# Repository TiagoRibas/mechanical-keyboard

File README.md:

# mechanical-keyboard
Projetos de teclado mecanico

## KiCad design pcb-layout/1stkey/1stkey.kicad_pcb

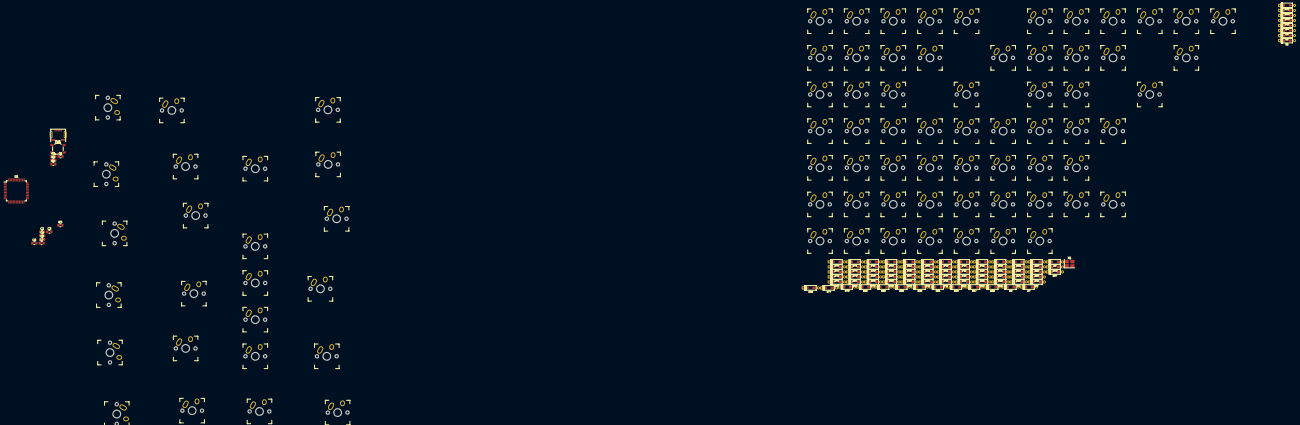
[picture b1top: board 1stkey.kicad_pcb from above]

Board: 2 copper layers, 183 parts (0 on the bottom side), 109 nets, no tracks yet.

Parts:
C1, C2: C_Small; C_0805_2012Metric_Pad1.15x1.40mm_HandSolder
C3: 1u; C_0805_2012Metric_Pad1.15x1.40mm_HandSolder
C4, C5, C6: 0,1u; C_0805_2012Metric_Pad1.15x1.40mm_HandSolder
C7: 4,7u; C_0805_2012Metric_Pad1.15x1.40mm_HandSolder
D1, D2, D3, D4, D5, D6, D7, D8, D9, D10, D11, D12, D13, D14, D15, D16, D17, D18, D19, D20, D21, D22, D23, D24, D25, D26, D27, D28, D29, D30, D31, D32, D33, D34, D35, D36, D37, D38, D39, D40, D41, D42, D43, D44, D45, D46, D47, D48, D49, D50, D51, D52, D53, D54, D55, D56, D57, D58, D59, D60, D61, D62, D63, D64, D65, D66, D67, D68, D69, D70, D71, D72, D73, D74, D75, D76, D77, D78, D79, D80, D81, D82, D83, D84: D; D_SOD123_axial
J1: USB_mini_micro_B; USB_miniB_hirose_5S8
K1, K2, K3, K4, K5, K6, K7, K8, K9, K10, K11, K12, K13, K14, K15, K16, K17, K18, K19, K20, K21, K22, K23, K24, K25, K26, K27, K28, K29, K30, K31, K32, K33, K34, K35, K36, K37, K38, K39, K40, K41, K42, K43, K44, K45, K46, K47, K48, K49, K50, K51, K52, K53, K54, K55, K56, K57, K58, K59, K60, K61, K62, K63, K64, K65, K66, K67, K68, K69, K70, K71, K72, K73, K74, K75, K76, K77, K78, K79, K80, K81, K82, K83, K84: KEYSW; Mx_Alps_100
R1, R4: 10K; R_0805_2012Metric_Pad1.15x1.40mm_HandSolder
R2, R3: 22; R_0805_2012Metric_Pad1.15x1.40mm_HandSolder
SW1: SW_PUSH; SW_SPST_TL3342
U1: ATMEGA32U4; TQFP-44_10x10mm_P0.8mm
X1: XTAL_GND; Crystal_SMD_SeikoEpson_TSX3225-4Pin_3.2x2.5mm_HandSoldering

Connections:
/col0: K1.1, K2.1, K3.1, K4.1, K5.1, K6.1, U1.41
/col1: K7.1, K8.1, K9.1, K10.1, K11.1, K12.1, U1.40
/col2: K13.1, K14.1, K15.1, K16.1, K17.1, K18.1
/col3: K19.1, K20.1, K21.1, K22.1, K23.1, K24.1
/col4: K25.1, K26.1, K27.1, K28.1, K29.1, K30.1
/col5: K31.1, K32.1, K33.1, K34.1, K35.1, K36.1
/col6: K37.1, K38.1, K39.1, K40.1, K41.1, K42.1
/col7: K43.1, K44.1, K45.1, K46.1, K47.1, K48.1
/col8: K49.1, K50.1, K51.1, K52.1, K53.1, K54.1
/col9: K55.1, K56.1, K57.1, K58.1, K59.1, K60.1
/col10: K61.1, K62.1, K63.1, K64.1, K65.1, K66.1
/col11: K67.1, K68.1, K69.1, K70.1, K71.1, K72.1
/col12: K73.1, K74.1, K75.1, K76.1, K77.1, K78.1
/col13: K79.1, K80.1, K81.1, K82.1, K83.1, K84.1
/row0: D1.1, D7.1, D13.1, D19.1, D25.1, D31.1, D37.1, D43.1, D49.1, D55.1, D61.1, D67.1, D73.1, D79.1, U1.39
/row1: D2.1, D8.1, D14.1, D20.1, D26.1, D32.1, D38.1, D44.1, D50.1, D56.1, D62.1, D68.1, D74.1, D80.1, U1.38
/row2: D3.1, D9.1, D15.1, D21.1, D27.1, D33.1, D39.1, D45.1, D51.1, D57.1, D63.1, D69.1, D75.1, D81.1
/row3: D4.1, D10.1, D16.1, D22.1, D28.1, D34.1, D40.1, D46.1, D52.1, D58.1, D64.1, D70.1, D76.1, D82.1
/row4: D5.1, D11.1, D17.1, D23.1, D29.1, D35.1, D41.1, D47.1, D53.1, D59.1, D65.1, D71.1, D77.1, D83.1
/row5: D6.1, D12.1, D18.1, D24.1, D30.1, D36.1, D42.1, D48.1, D54.1, D60.1, D66.1, D72.1, D78.1, D84.1
GND: C1.2, C2.2, C3.2, C4.2, C5.2, C6.2, C7.2, J1.5, J1.6, R4.2, SW1.1, U1.5, U1.15, U1.23, U1.35, U1.43, X1.3
unnamed: C1.1, U1.16, X1.1
unnamed: C2.1, U1.17, X1.2
unnamed: C3.1, U1.6
unnamed: D1.2, K1.2
unnamed: D2.2, K2.2
unnamed: D3.2, K3.2
unnamed: D4.2, K4.2
unnamed: D5.2, K5.2
unnamed: D6.2, K6.2
unnamed: D7.2, K7.2
unnamed: D8.2, K8.2
unnamed: D9.2, K9.2
unnamed: D10.2, K10.2
unnamed: D11.2, K11.2
unnamed: D12.2, K12.2
unnamed: D13.2, K13.2
unnamed: D14.2, K14.2
unnamed: D15.2, K15.2
unnamed: D16.2, K16.2
unnamed: D17.2, K17.2
unnamed: D18.2, K18.2
unnamed: D19.2, K19.2
unnamed: D20.2, K20.2
unnamed: D21.2, K21.2
unnamed: D22.2, K22.2
unnamed: D23.2, K23.2
unnamed: D24.2, K24.2
unnamed: D25.2, K25.2
unnamed: D26.2, K26.2
unnamed: D27.2, K27.2
unnamed: D28.2, K28.2
unnamed: D29.2, K29.2
unnamed: D30.2, K30.2
unnamed: D31.2, K31.2
unnamed: D32.2, K32.2
unnamed: D33.2, K33.2
unnamed: D34.2, K34.2
unnamed: D35.2, K35.2
unnamed: D36.2, K36.2
unnamed: D37.2, K37.2
unnamed: D38.2, K38.2
unnamed: D39.2, K39.2
unnamed: D40.2, K40.2
unnamed: D41.2, K41.2
unnamed: D42.2, K42.2
unnamed: D43.2, K43.2
unnamed: D44.2, K44.2
unnamed: D45.2, K45.2
unnamed: D46.2, K46.2
unnamed: D47.2, K47.2
unnamed: D48.2, K48.2
unnamed: D55.2, K55.2
unnamed: D56.2, K56.2
unnamed: D57.2, K57.2
unnamed: D58.2, K58.2
unnamed: D59.2, K59.2
unnamed: D60.2, K60.2
unnamed: D61.2, K61.2
unnamed: D62.2, K62.2
unnamed: D63.2, K63.2
unnamed: D64.2, K64.2
unnamed: D65.2, K65.2
unnamed: D66.2, K66.2
unnamed: D67.2, K67.2
unnamed: D68.2, K68.2
unnamed: D69.2, K69.2
unnamed: D70.2, K70.2
unnamed: D71.2, K71.2
unnamed: D72.2, K72.2
unnamed: D73.2, K73.2
unnamed: D74.2, K74.2
unnamed: D75.2, K75.2
unnamed: D76.2, K76.2
unnamed: D77.2, K77.2
unnamed: D78.2, K78.2
unnamed: D79.2, K79.2
unnamed: D80.2, K80.2
unnamed: D81.2, K81.2
unnamed: D82.2, K82.2
unnamed: D83.2, K83.2
unnamed: D84.2, K84.2
unnamed: J1.2, R2.2
unnamed: J1.3, R3.2
unnamed: R1.1, SW1.2, U1.13
unnamed: R2.1, U1.3
unnamed: R3.1, U1.4
unnamed: R4.1, U1.33
VCC: C4.1, C5.1, C6.1, C7.1, J1.1, R1.2, U1.2, U1.14, U1.24, U1.34, U1.44

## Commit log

2019-04-24 Footprints e componentes adicionados
2019-04-24 Layout criado
2019-05-09 pcb começando a ser projetado
